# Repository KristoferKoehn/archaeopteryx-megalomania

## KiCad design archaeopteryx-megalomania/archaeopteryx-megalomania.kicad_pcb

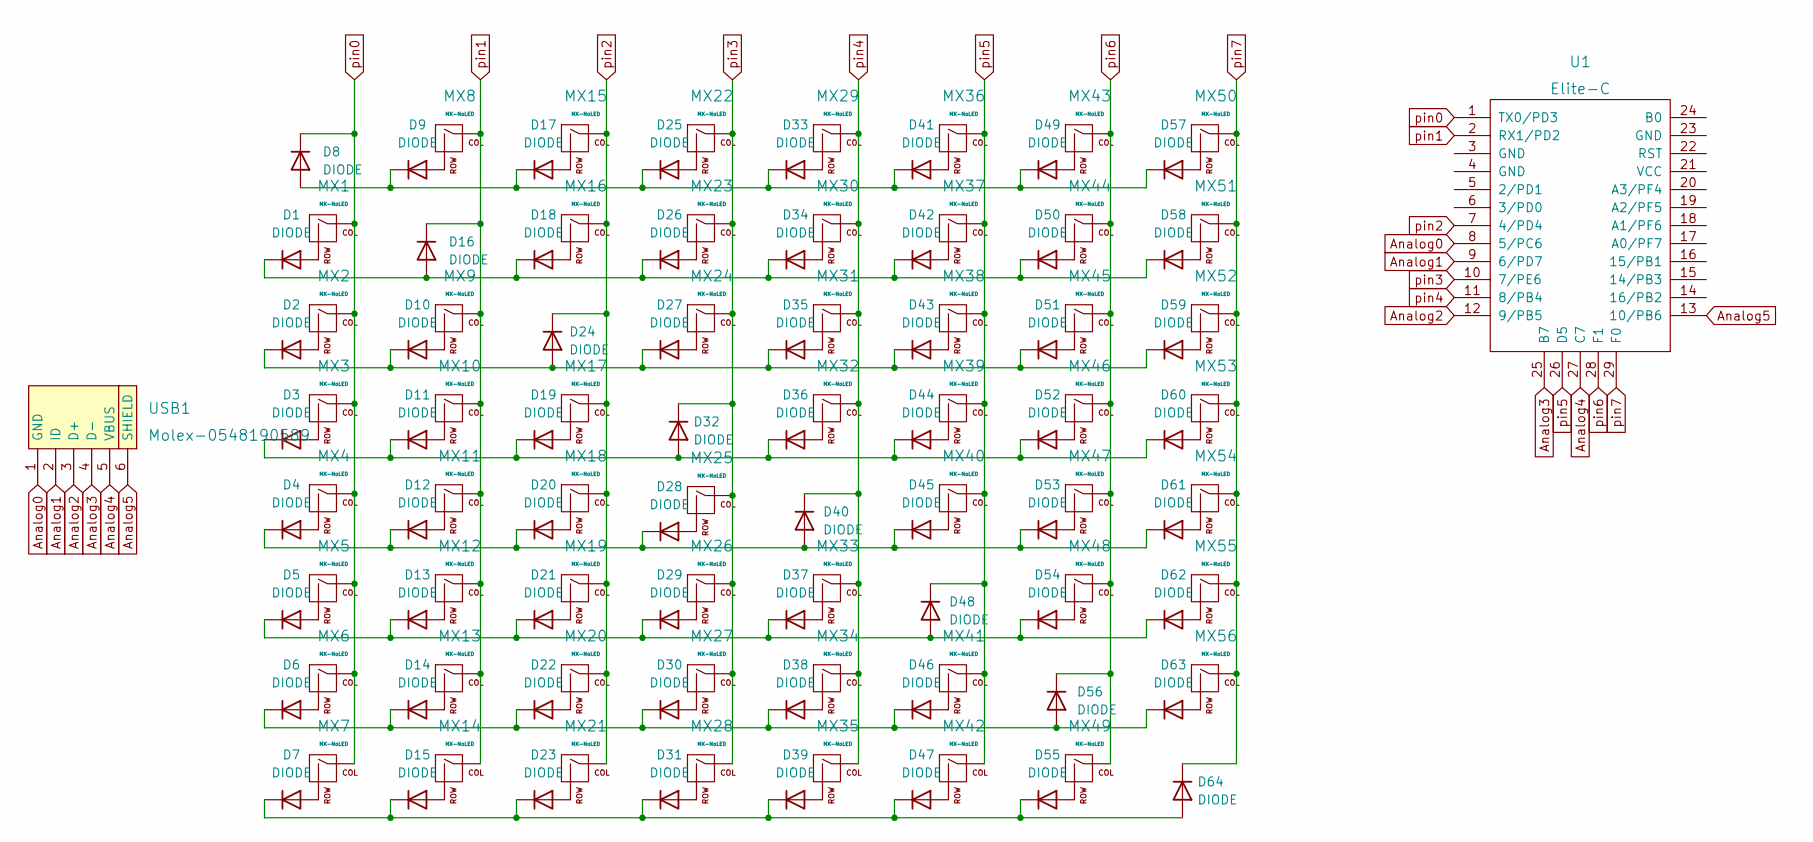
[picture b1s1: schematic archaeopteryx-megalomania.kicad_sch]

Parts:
D1, D2, D3, D4, D5, D6, D7, D8, D9, D10, D11, D12, D13, D14, D15, D16, D17, D18, D19, D20, D21, D22, D23, D24, D25, D26, D27, D28, D29, D30, D31, D32, D33, D34, D35, D36, D37, D38, D39, D40, D41, D42, D43, D44, D45, D46, D47, D48, D49, D50, D51, D52, D53, D54, D55, D56, D57, D58, D59, D60, D61, D62, D63, D64: DIODE; Diode-Hybrid-Back
MX1, MX2, MX3, MX4, MX5, MX6, MX7, MX8, MX9, MX10, MX11, MX12, MX13, MX14, MX15, MX16, MX17, MX18, MX19, MX20, MX21, MX22, MX23, MX24, MX25, MX26, MX27, MX28, MX29, MX30, MX31, MX32, MX33, MX34, MX35, MX36, MX37, MX38, MX39, MX40, MX41, MX42, MX43, MX44, MX45, MX46, MX47, MX48, MX49, MX50, MX51, MX52, MX53, MX54, MX55, MX56: MX-NoLED; Triple-Dual-1u-NoLED
U1: Elite-C
USB1: Molex-0548190589; Header-6-Pin-ZigZag-AnalogBreakout

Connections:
Analog0: U1.8 (5/PC6), USB1.1 (GND)
Analog1: U1.9 (6/PD7), USB1.2 (ID)
Analog2: U1.12 (9/PB5), USB1.3 (D+)
Analog3: U1.25 (B7), USB1.4 (D-)
Analog4: U1.27 (C7), USB1.5 (VBUS)
Analog5: U1.13 (10/PB6), USB1.6 (SHIELD)
unnamed: D1.1 (A), MX1.2 (ROW)
unnamed: D1.2 (K), D16.1 (A), D18.2 (K), D26.2 (K), D34.2 (K), D42.2 (K), D50.2 (K), D58.2 (K)
unnamed: D2.1 (A), MX2.2 (ROW)
unnamed: D3.1 (A), MX3.2 (ROW)
unnamed: D4.1 (A), MX4.2 (ROW)
unnamed: D5.1 (A), MX5.2 (ROW)
unnamed: D6.1 (A), MX6.2 (ROW)
unnamed: D7.1 (A), MX7.2 (ROW)
unnamed: D9.1 (A), MX8.2 (ROW)
unnamed: D10.1 (A), MX9.2 (ROW)
unnamed: D2.2 (K), D10.2 (K), D24.1 (A), D27.2 (K), D35.2 (K), D43.2 (K), D51.2 (K), D59.2 (K)
unnamed: D11.1 (A), MX10.2 (ROW)
unnamed: D3.2 (K), D11.2 (K), D19.2 (K), D32.1 (A), D36.2 (K), D44.2 (K), D52.2 (K), D60.2 (K)
unnamed: D12.1 (A), MX11.2 (ROW)
unnamed: D4.2 (K), D12.2 (K), D20.2 (K), D28.2 (K), D40.1 (A), D45.2 (K), D53.2 (K), D61.2 (K)
unnamed: D13.1 (A), MX12.2 (ROW)
unnamed: D5.2 (K), D13.2 (K), D21.2 (K), D29.2 (K), D37.2 (K), D48.1 (A), D54.2 (K), D62.2 (K)
unnamed: D14.1 (A), MX13.2 (ROW)
unnamed: D6.2 (K), D14.2 (K), D22.2 (K), D30.2 (K), D38.2 (K), D46.2 (K), D56.1 (A), D63.2 (K)
unnamed: D15.1 (A), MX14.2 (ROW)
unnamed: D7.2 (K), D15.2 (K), D23.2 (K), D31.2 (K), D39.2 (K), D47.2 (K), D55.2 (K), D64.1 (A)
unnamed: D17.1 (A), MX15.2 (ROW)
unnamed: D8.1 (A), D9.2 (K), D17.2 (K), D25.2 (K), D33.2 (K), D41.2 (K), D49.2 (K), D57.2 (K)
unnamed: D18.1 (A), MX16.2 (ROW)
unnamed: D19.1 (A), MX17.2 (ROW)
unnamed: D20.1 (A), MX18.2 (ROW)
unnamed: D21.1 (A), MX19.2 (ROW)
unnamed: D22.1 (A), MX20.2 (ROW)
unnamed: D23.1 (A), MX21.2 (ROW)
unnamed: D25.1 (A), MX22.2 (ROW)
unnamed: D26.1 (A), MX23.2 (ROW)
unnamed: D27.1 (A), MX24.2 (ROW)
unnamed: D28.1 (A), MX25.2 (ROW)
unnamed: D29.1 (A), MX26.2 (ROW)
unnamed: D30.1 (A), MX27.2 (ROW)
unnamed: D31.1 (A), MX28.2 (ROW)
unnamed: D33.1 (A), MX29.2 (ROW)
unnamed: D34.1 (A), MX30.2 (ROW)
unnamed: D35.1 (A), MX31.2 (ROW)
unnamed: D36.1 (A), MX32.2 (ROW)
unnamed: D37.1 (A), MX33.2 (ROW)
unnamed: D38.1 (A), MX34.2 (ROW)
unnamed: D39.1 (A), MX35.2 (ROW)
unnamed: D41.1 (A), MX36.2 (ROW)
unnamed: D42.1 (A), MX37.2 (ROW)
unnamed: D43.1 (A), MX38.2 (ROW)
unnamed: D44.1 (A), MX39.2 (ROW)
unnamed: D45.1 (A), MX40.2 (ROW)
unnamed: D46.1 (A), MX41.2 (ROW)
unnamed: D47.1 (A), MX42.2 (ROW)
unnamed: D49.1 (A), MX43.2 (ROW)
unnamed: D50.1 (A), MX44.2 (ROW)
unnamed: D51.1 (A), MX45.2 (ROW)
unnamed: D52.1 (A), MX46.2 (ROW)
unnamed: D53.1 (A), MX47.2 (ROW)
unnamed: D54.1 (A), MX48.2 (ROW)
unnamed: D55.1 (A), MX49.2 (ROW)
unnamed: D57.1 (A), MX50.2 (ROW)
unnamed: D58.1 (A), MX51.2 (ROW)
unnamed: D59.1 (A), MX52.2 (ROW)
unnamed: D60.1 (A), MX53.2 (ROW)
unnamed: D61.1 (A), MX54.2 (ROW)
unnamed: D62.1 (A), MX55.2 (ROW)
unnamed: D63.1 (A), MX56.2 (ROW)
pin0: D8.2 (K), MX1.1 (COL), MX2.1 (COL), MX3.1 (COL), MX4.1 (COL), MX5.1 (COL), MX6.1 (COL), MX7.1 (COL), U1.1 (TX0/PD3)
pin1: D16.2 (K), MX8.1 (COL), MX9.1 (COL), MX10.1 (COL), MX11.1 (COL), MX12.1 (COL), MX13.1 (COL), MX14.1 (COL), U1.2 (RX1/PD2)
pin2: D24.2 (K), MX15.1 (COL), MX16.1 (COL), MX17.1 (COL), MX18.1 (COL), MX19.1 (COL), MX20.1 (COL), MX21.1 (COL), U1.7 (4/PD4)
pin3: D32.2 (K), MX22.1 (COL), MX23.1 (COL), MX24.1 (COL), MX25.1 (COL), MX26.1 (COL), MX27.1 (COL), MX28.1 (COL), U1.10 (7/PE6)
pin4: D40.2 (K), MX29.1 (COL), MX30.1 (COL), MX31.1 (COL), MX32.1 (COL), MX33.1 (COL), MX34.1 (COL), MX35.1 (COL), U1.11 (8/PB4)
pin5: D48.2 (K), MX36.1 (COL), MX37.1 (COL), MX38.1 (COL), MX39.1 (COL), MX40.1 (COL), MX41.1 (COL), MX42.1 (COL), U1.26 (D5)
pin6: D56.2 (K), MX43.1 (COL), MX44.1 (COL), MX45.1 (COL), MX46.1 (COL), MX47.1 (COL), MX48.1 (COL), MX49.1 (COL), U1.28 (F1)
pin7: D64.2 (K), MX50.1 (COL), MX51.1 (COL), MX52.1 (COL), MX53.1 (COL), MX54.1 (COL), MX55.1 (COL), MX56.1 (COL), U1.29 (F0)

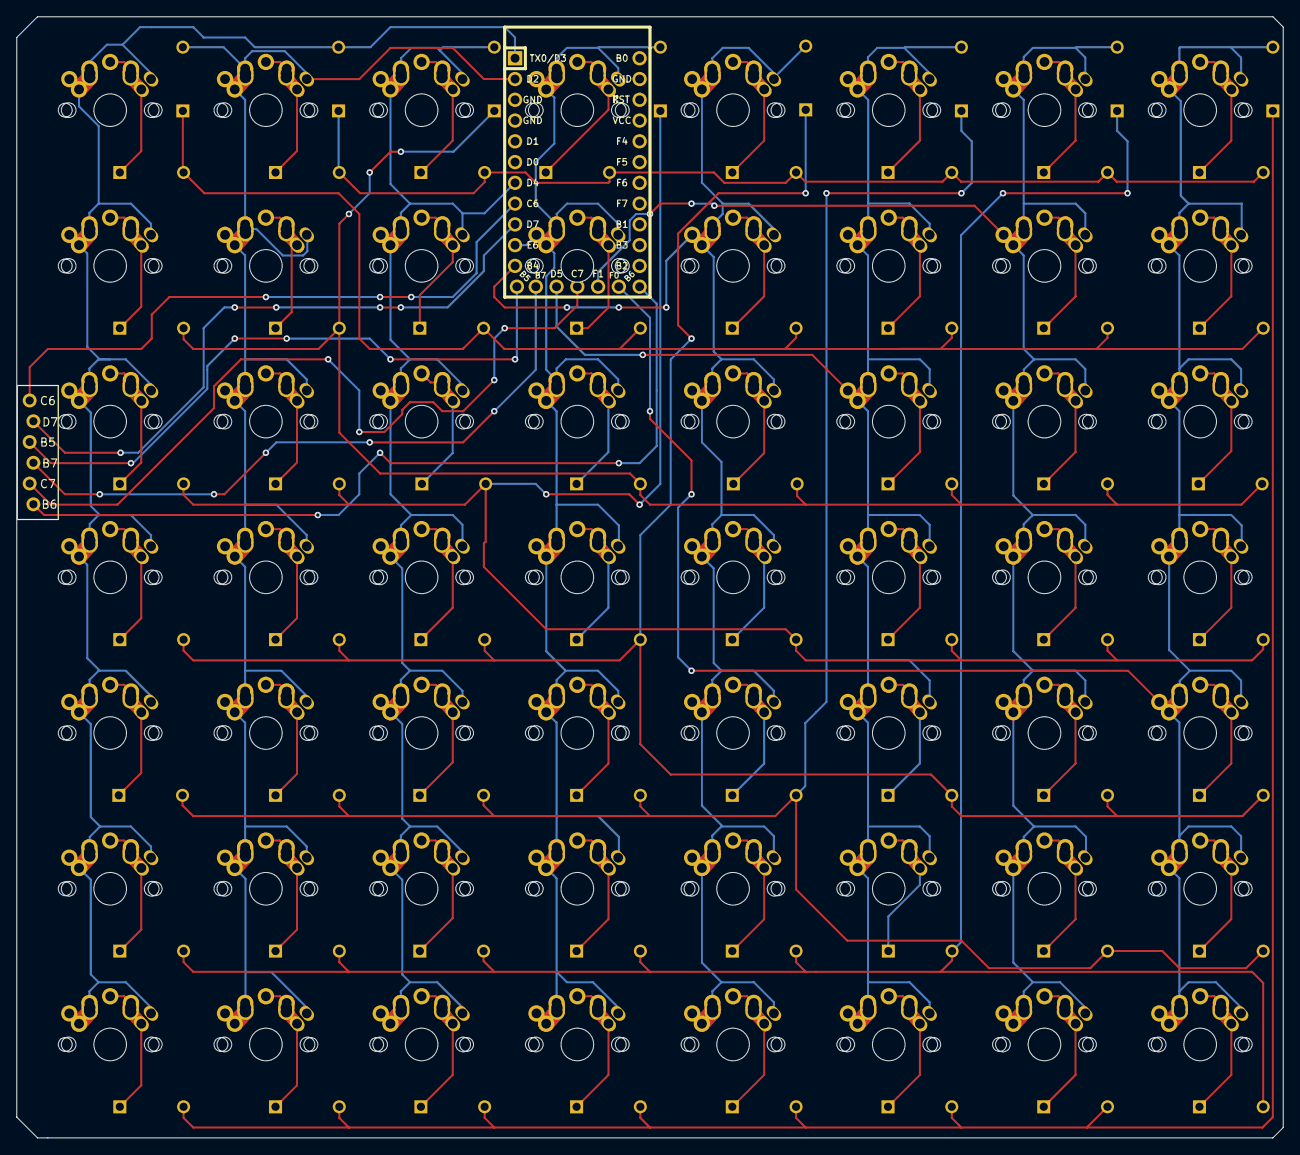
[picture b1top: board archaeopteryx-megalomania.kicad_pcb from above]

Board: 2 copper layers, 154.9 x 137.2 mm, 122 parts (0 on the bottom side), 78 nets.

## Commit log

2022-09-14 first rev
